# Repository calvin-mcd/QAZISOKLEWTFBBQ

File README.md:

# QAZISOKLEWTFBBQ

QAZISOKLEWTFBBQ is an idea for a keyboard by summerqm and haha from the 40s discord community. The layout is by summerqm & haha. Silkscreen is by Summerqm. Pcb design by me. Upcoming case is by _obabo.

The project takes design cues from the amazing [qaz](https://cbkbd.bigcartel.com/product/qaz), [vault35](https://mechvault.net/products/vault-35-mini-keyboard) and [hull](https://trashman.wiki/en/cases/hull) boards.

The board is a qaz-like pcb in hhkb-style that supports ISO enter & one rotary encoder. This is a simple pcb design using the micro controller [rp2040-zero](https://www.waveshare.com/rp2040-zero.htm) that supports both throughhole and smd diodes.

The pcb is designed to be used plateless and supports both hull-style and vault-like mounting.

## Layout

[Link](http://www.keyboard-layout-editor.com/#/gists/4e032fd765729241acc9e978638f968c)

## Images

## Case

_obabo made rad little case for it which uses the hull-style mounting. The case file is designed to use m2.5 heat-inserts and screws such as these:

https://www.mcmaster.com/94459A439/

https://www.mcmaster.com/94500A213/

check out _obabo's other amazing case designs here: https://github.com/m0110
  
## Todo

- [ ] order & test pcb
- [ ] create firmware
- [ ] create & test case

## Disclaimer

Please note that this project is a work in progress with no guarantees of a working outcome. No-one involved in this project is responsible for any usage issues that may arise. However, feel free to edit, modify and otherwise utilise these files.

## License

This project is released under the GPL v3 License. Please refer to the LICENCE file.

## Credits

big thanks to summerqm, haha & _obabo.

As always big thanks also to the many people who inspired and helped with this board!

Any questions, contact Calvin0563 on Discord.

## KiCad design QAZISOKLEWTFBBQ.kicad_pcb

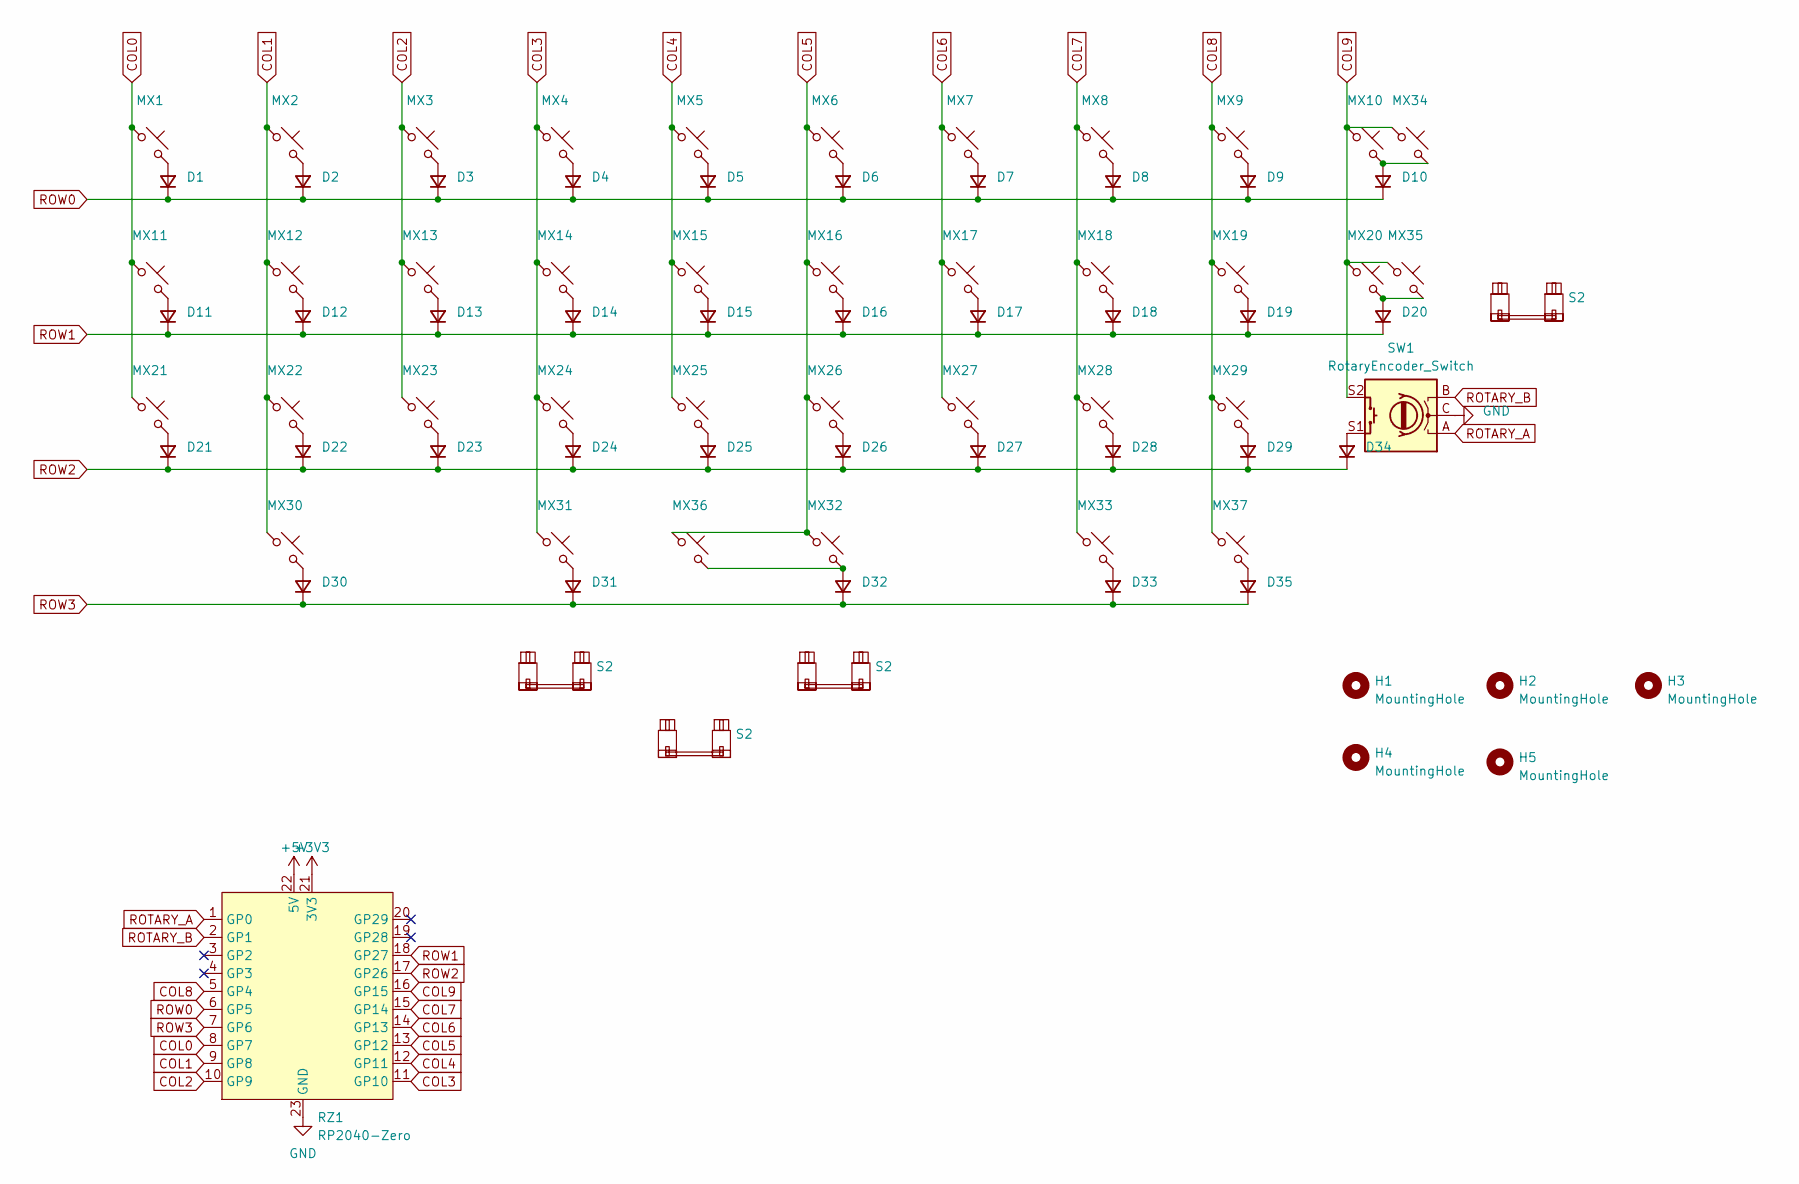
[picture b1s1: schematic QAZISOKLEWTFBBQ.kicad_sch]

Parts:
D1, D2, D3, D4, D5, D6, D7, D8, D9, D10, D11, D12, D13, D14, D15, D16, D17, D18, D19, D20, D21, D22, D23, D24, D25, D26, D27, D28, D29, D30, D31, D32, D33, D34, D35: D_Small; Diode-Hybrid-Back
H1, H2, H3, H4, H5: MountingHole; MountingHole_2.2mm_M2
MX1, MX2, MX3, MX4, MX5, MX6, MX7, MX8, MX9, MX12, MX13, MX14, MX15, MX16, MX17, MX18, MX19, MX20, MX22, MX23, MX24, MX25, MX26, MX27, MX28, MX29, MX31, MX32, MX34, MX36: MX_SW_solder; SW_MX_1u
MX10: MX_SW_solder; SW_MX_1.75u
MX11, MX30, MX33, MX37: MX_SW_solder; SW_MX_1.25u
MX21, MX35: MX_SW_solder; SW_MX_1.5u
RZ1: RP2040-Zero; rp2040-zero-tht
S2: MX_stab; STAB_MX_6u
SW1: RotaryEncoder_Switch; RotaryEncoder_EC11

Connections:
+3V3: RZ1.21 (3V3)
+5V: RZ1.22 (5V)
COL0: MX1.1, MX11.1, MX21.1, RZ1.8 (GP7)
COL1: MX2.1, MX12.1, MX22.1, MX30.1, RZ1.9 (GP8)
COL2: MX3.1, MX13.1, MX23.1, RZ1.10 (GP9)
COL3: MX4.1, MX14.1, MX24.1, MX31.1, RZ1.11 (GP10)
COL4: MX5.1, MX15.1, MX25.1, RZ1.12 (GP11)
COL5: MX6.1, MX16.1, MX26.1, MX32.1, MX36.1, RZ1.13 (GP12)
COL6: MX7.1, MX17.1, MX27.1, RZ1.14 (GP13)
COL7: MX8.1, MX18.1, MX28.1, MX33.1, RZ1.15 (GP14)
COL8: MX9.1, MX19.1, MX29.1, MX37.1, RZ1.5 (GP4)
COL9: MX10.1, MX20.1, MX34.1, MX35.1, RZ1.16 (GP15), SW1.S2
GND: RZ1.23 (GND), SW1.C
unnamed: D1.2 (A), MX1.2
unnamed: D2.2 (A), MX2.2
unnamed: D3.2 (A), MX3.2
unnamed: D4.2 (A), MX4.2
unnamed: D5.2 (A), MX5.2
unnamed: D6.2 (A), MX6.2
unnamed: D7.2 (A), MX7.2
unnamed: D8.2 (A), MX8.2
unnamed: D9.2 (A), MX9.2
unnamed: D10.2 (A), MX10.2, MX34.2
unnamed: D11.2 (A), MX11.2
unnamed: D12.2 (A), MX12.2
unnamed: D13.2 (A), MX13.2
unnamed: D14.2 (A), MX14.2
unnamed: D15.2 (A), MX15.2
unnamed: D16.2 (A), MX16.2
unnamed: D17.2 (A), MX17.2
unnamed: D18.2 (A), MX18.2
unnamed: D19.2 (A), MX19.2
unnamed: D20.2 (A), MX20.2, MX35.2
unnamed: D21.2 (A), MX21.2
unnamed: D22.2 (A), MX22.2
unnamed: D23.2 (A), MX23.2
unnamed: D24.2 (A), MX24.2
unnamed: D25.2 (A), MX25.2
unnamed: D26.2 (A), MX26.2
unnamed: D27.2 (A), MX27.2
unnamed: D28.2 (A), MX28.2
unnamed: D29.2 (A), MX29.2
unnamed: D30.2 (A), MX30.2
unnamed: D31.2 (A), MX31.2
unnamed: D32.2 (A), MX32.2, MX36.2
unnamed: D33.2 (A), MX33.2
unnamed: D34.2 (A), SW1.S1
unnamed: D35.2 (A), MX37.2
ROTARY_A: RZ1.1 (GP0), SW1.A
ROTARY_B: RZ1.2 (GP1), SW1.B
ROW0: D1.1 (K), D2.1 (K), D3.1 (K), D4.1 (K), D5.1 (K), D6.1 (K), D7.1 (K), D8.1 (K), D9.1 (K), D10.1 (K), RZ1.6 (GP5)
ROW1: D11.1 (K), D12.1 (K), D13.1 (K), D14.1 (K), D15.1 (K), D16.1 (K), D17.1 (K), D18.1 (K), D19.1 (K), D20.1 (K), RZ1.18 (GP27)
ROW2: D21.1 (K), D22.1 (K), D23.1 (K), D24.1 (K), D25.1 (K), D26.1 (K), D27.1 (K), D28.1 (K), D29.1 (K), D34.1 (K), RZ1.17 (GP26)
ROW3: D30.1 (K), D31.1 (K), D32.1 (K), D33.1 (K), D35.1 (K), RZ1.7 (GP6)

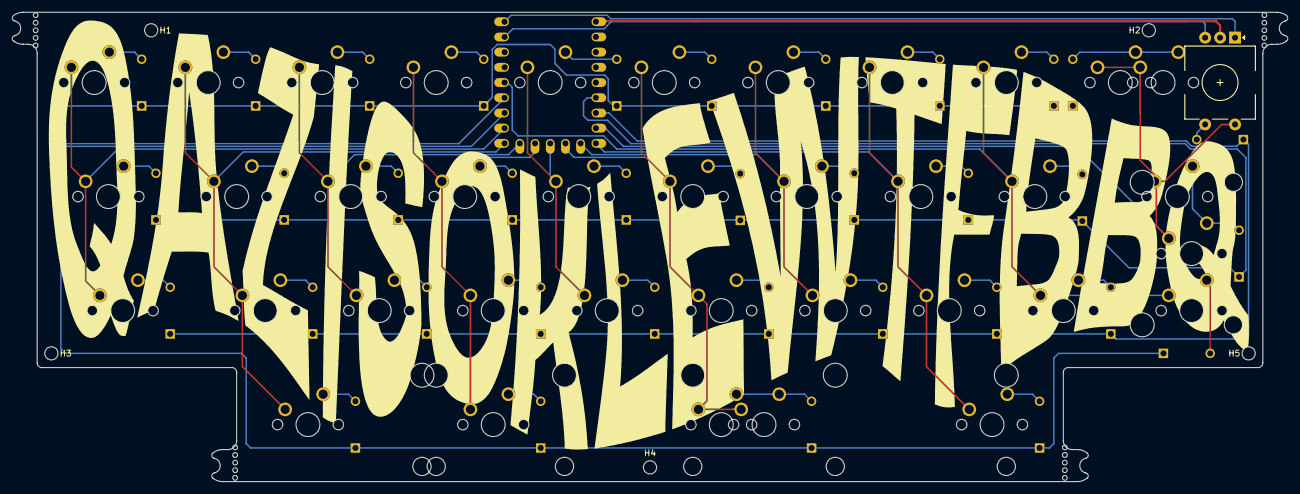
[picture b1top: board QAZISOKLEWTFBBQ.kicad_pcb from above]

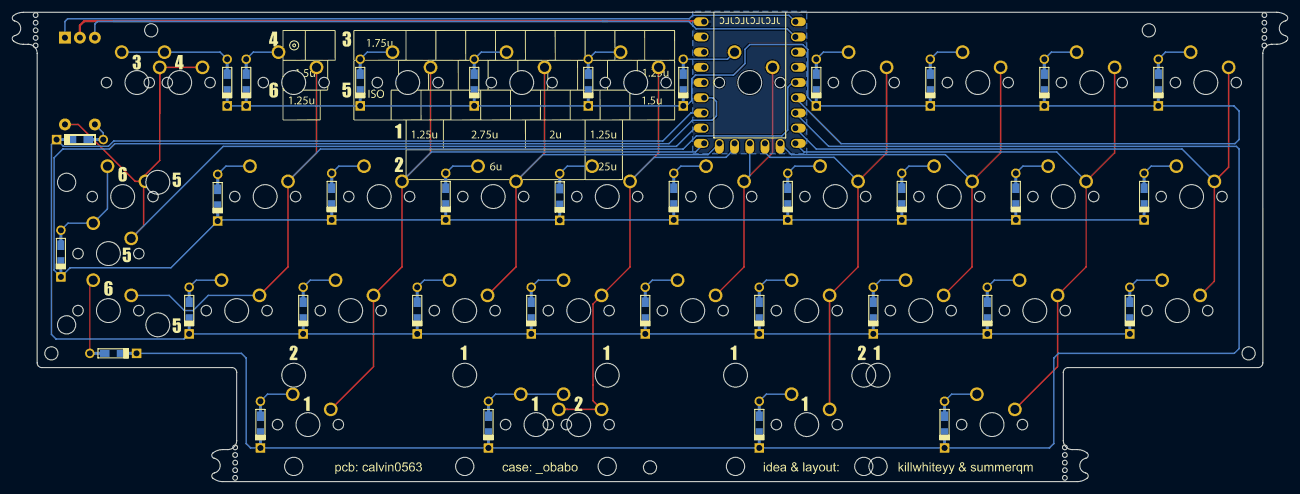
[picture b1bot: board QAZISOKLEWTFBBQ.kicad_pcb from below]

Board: 2 copper layers, 213.1 x 78.4 mm, 83 parts (6 on the bottom side), 52 nets.

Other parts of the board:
S1: MX_stab; STAB_MX_2u
S3: MX_stab; STAB_MX_ISO-ROT
S4: MX_stab; STAB_MX_6u

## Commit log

2023-08-24 initialise
2023-08-24 added pcb renders
2023-08-29 backup
2023-11-17 update readme, fresh pcb step
2024-02-06 added case file, update readme
